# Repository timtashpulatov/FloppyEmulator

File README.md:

# YetAnotherFloppyEmulator
Oh no, not another floppy emulator please

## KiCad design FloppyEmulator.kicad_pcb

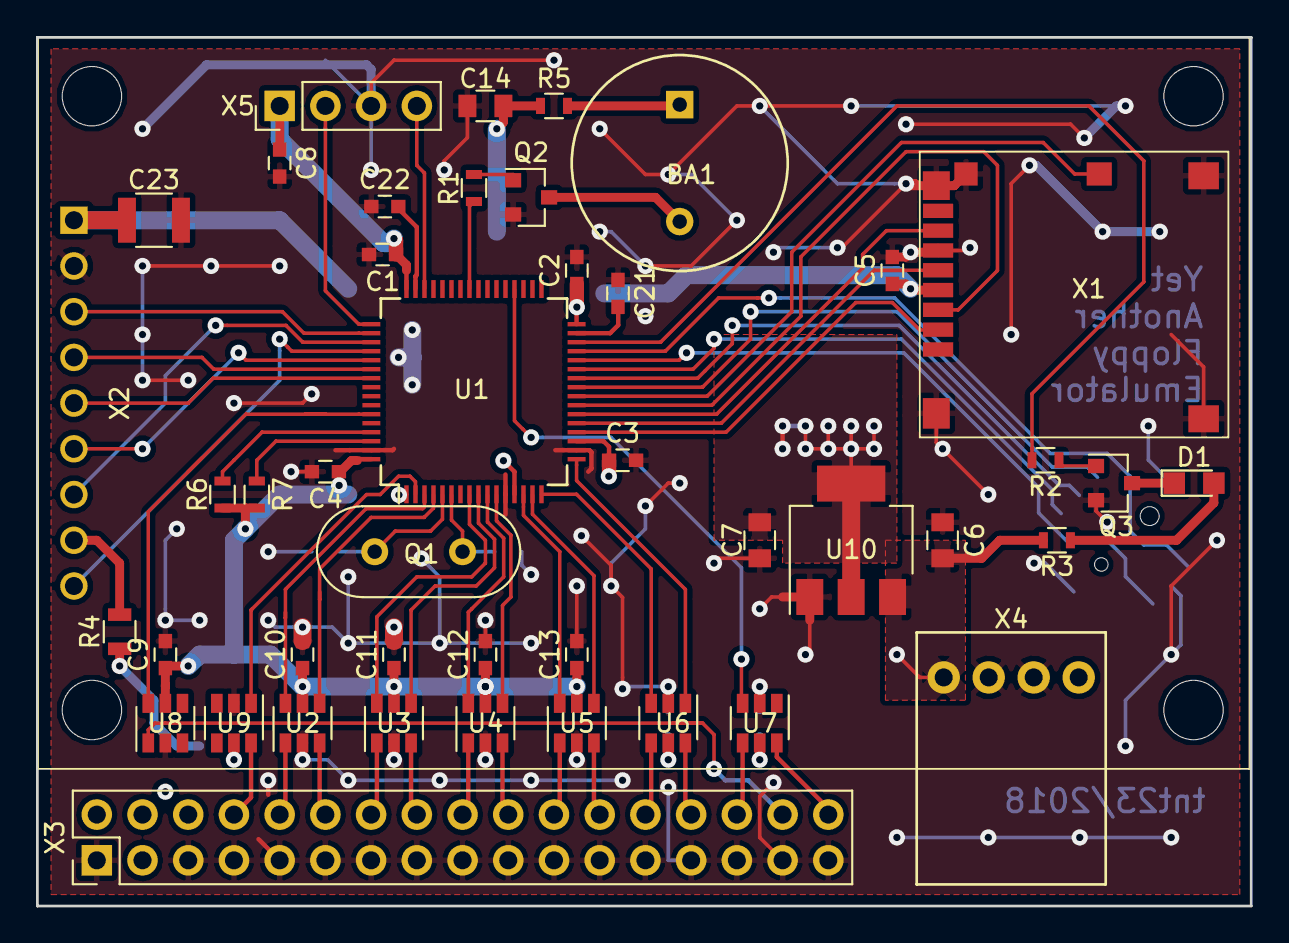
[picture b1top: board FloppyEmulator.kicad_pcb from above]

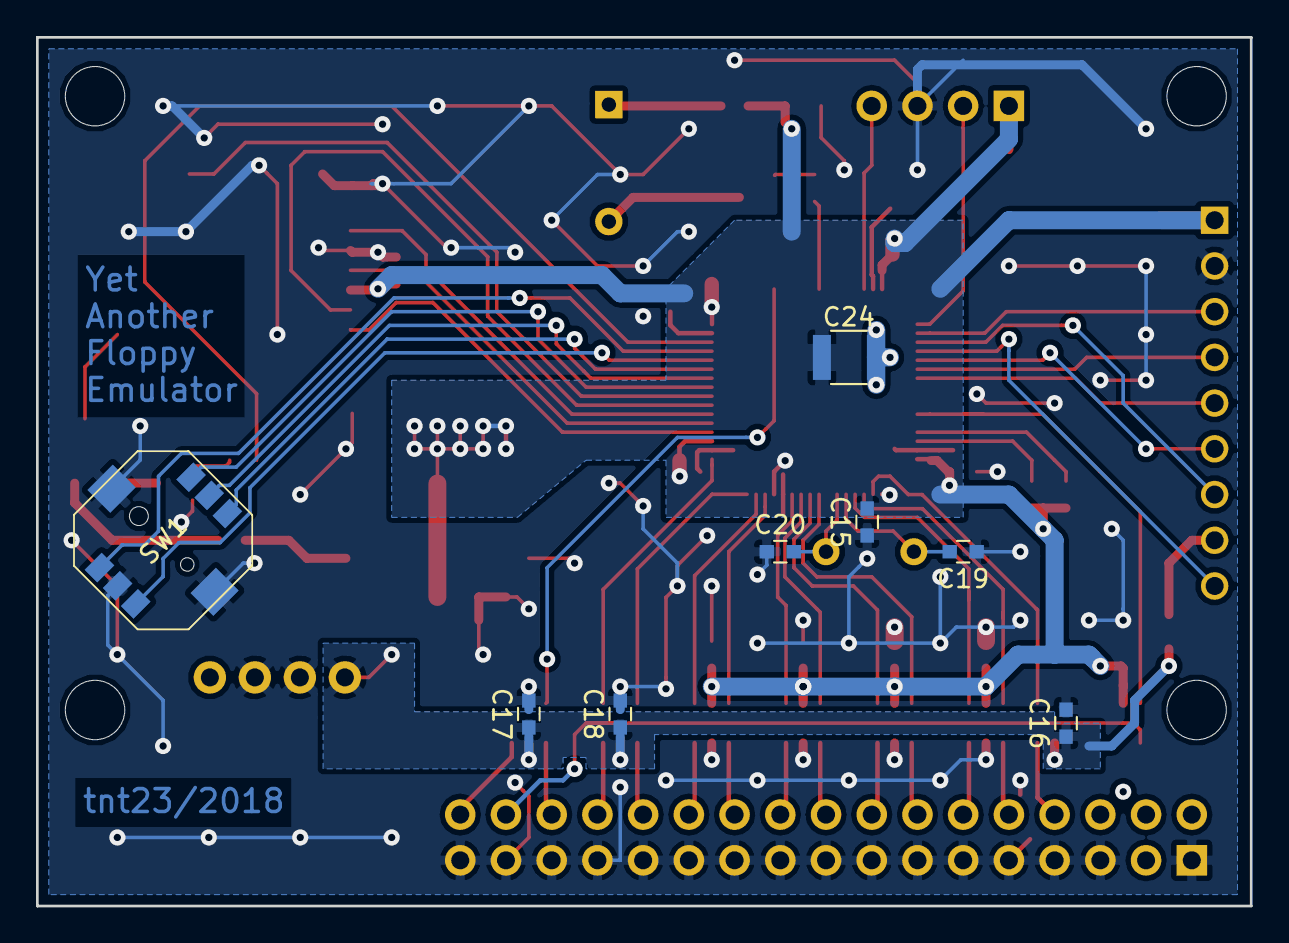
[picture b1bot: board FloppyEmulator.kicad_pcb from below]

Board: 2 copper layers, 67.4 x 48.3 mm, 52 parts (8 on the bottom side), 63 nets.

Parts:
BA1: HCM1206A
C1, C2, C3, C4, C5, C8, C9, C10, C11, C12, C13, C15, C16, C17, C18, C21, C22: 0,1; C_0603
C6, C7, C14: 2u2; C_0805
C19, C20: 15pF; C_0603
C23, C24: 10u; C_1210
D1: LED_ALT; LED_0805
Q1: Crystal_GND24; Crystal_HC49-U_Vertical
Q2, Q3: BC817; SOT-23
R1, R2: 10K; R_0603
R3: 220; R_0603
R4: TBD; R_0805
R5: TBD; R_0603
R6, R7: DNF; R_0603
SW1: ALPS_5WAY; ALPS_SKRHABE010
U1: STM32F405RGTx; LQFP-64_10x10mm_Pitch0.5mm
U2, U3, U4, U5, U6, U7, U8, U9: SN74LVC2G07; SOT-23-6
U10: AP1117-15; SOT-223-3_TabPin2
X1: Micro_SD_Card_Det; MOLEX_5027740891
X2: Conn_01x09; QVGA_LCD_9pin
X3: Conn_02x17_Odd_Even; Pin_Header_Straight_2x17_Pitch2.54mm
X4: TE 171826-4; 171826-4
X5: SWD; Pin_Header_Straight_1x04_Pitch2.54mm

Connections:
+3V3: C1.1, C2.1, C3.1, C4.1, C5.1, C7.1, C8.1, C9.1, C10.1, C11.1, C12.1, C13.1, C14.1, C15.2, C23.1, C24.1, R5.2, R6.2, R7.2, U1.1, U1.13, U1.19, U1.32, U1.48, U1.64, U2.5, U3.5, U4.5, U5.5, U8.5, U10.2, X1.4, X2.1, X5.1
+5VDC: C6.1, C16.1, C17.1, C18.1, R3.2, R4.1, U6.5, U7.5, U9.5, U10.3, X4.1
/BACKLIGHT: R4.2, X2.8
/BEEP: R1.2, U1.41
/BUTTON1: SW1.6, U1.29
/BUTTON2: SW1.1, U1.27
/BUTTON3: SW1.3, U1.25
/BUTTON4: SW1.4, U1.28
/BUTTON5: SW1.2, U1.26
/CARD_DETECT: U1.24, X1.10
/DIR: U1.11, U4.4
/INDEX: U1.2, U9.1
/LCD_DC: U1.55, X2.5
/LCD_RESET: U1.54, X2.4
/LED1: R2.2, U1.30
/OSC_IN: C19.2, Q1.2, U1.5
/OSC_OUT: C20.2, Q1.1, U1.6
/SEL0: U1.3, U2.6
/SEL1: U1.4, U2.4
/SEL2: U1.8, U3.6
/SEL3: U1.9, U3.4
/SIDE: U1.59, U8.6
/STEP: U1.10, U4.6
/SWCLK: U1.49, X5.2
/SWDIO: U1.46, X5.4
/TRACK0: U1.16, U6.3
/VCAP1: C21.2, U1.31
/VCAP2: C22.2, U1.47
/WPROT: U1.17, U6.1
/WRDATA: U1.14, U5.6
/WRGATE: U1.15, U5.4
GND: C1.2, C2.2, C3.2, C4.2, C5.2, C6.2, C7.2, C8.2, C9.2, C10.2, C11.2, C12.2, C13.2, C14.2, C15.1, C16.2, C17.2, C18.2, C19.1, C20.1, C21.1, C22.1, C23.2, C24.2, Q2.2, Q3.2, SW1.5, SW1.7, U1.12, U1.18, U1.63, U2.2, U3.2, U4.2, U5.2, U6.2, U7.2, U8.2, U9.2, U10.1, X1.6, X1.9, X1.11, X2.2, X3.1, X3.5, X3.7, X3.9, X3.11, X3.13, X3.15, X3.17, X3.19, X3.21, X3.23, X3.25, X3.27, X3.29, X3.31, X3.33, X4.2, X4.3, X5.3
unnamed: BA1.1, R5.1
unnamed: BA1.2, Q2.3
unnamed: D1.1, Q3.3
unnamed: D1.2, R3.1
unnamed: Q2.1, R1.1
unnamed: Q3.1, R2.1
unnamed: U2.1, X3.10
unnamed: U2.3, X3.12
unnamed: U3.1, X3.14
unnamed: U3.3, X3.16
unnamed: U4.1, X3.18
unnamed: U4.3, X3.20
unnamed: U5.1, X3.22
unnamed: U5.3, X3.24
unnamed: U6.4, X3.26
unnamed: U6.6, X3.28
unnamed: U7.4, X3.30
unnamed: U7.6, X3.34
unnamed: U8.1, X3.32
unnamed: U9.6, X3.8
SCL: R6.1, U1.61
SDA: R7.1, U1.62
SPI1_MISO: U1.22, X1.7
SPI1_MOSI: U1.23, X1.3
SPI1_NSS: U1.20, X1.2
SPI1_SCK: U1.21, X1.5
SPI2_MOSI: U1.36, U7.3
SPI3_MISO: U1.52, X2.9
SPI3_MOSI: U1.53, X2.6
SPI3_NSS: U1.50, X2.3
SPI3_SCK: U1.51, X2.7

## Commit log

2017-12-28 Bit of update
2017-12-28 Signals assigned
2017-12-28 Add microSD connector datasheet
2017-12-28 Add footprint library with LCD and microSD
2017-12-28 Draft components placement
2017-12-28 Add microSD footprint. Update schematic and PCB
2017-12-28 Add docs
2017-12-28 Add ALPS 5-way joystick
2017-12-28 Add FloppyEmulator library
2017-12-28 Add CubeMX layout pic. PCB remastered
2017-12-31 Layout and schematic update
2017-12-31 More docs and 3d models
2018-01-02 Caps added. PCB update
2018-01-02 Routing WIP
2018-01-02 Backlight
2018-01-02 Copper pours
2018-01-02 Add HCM1206A beeper
2018-01-02 Add I2C
2018-01-02 Bit of 3d models
2018-01-03 Add I2C pullups
2018-01-03 Cleanups
2018-01-03 Credits
2018-01-03 Even more cleanups
2018-01-03 LCD add-on board size corrected
2018-01-03 README.md updated
2018-01-03 Images
2018-01-03 PCB trimmed to updated LCD shield
2018-01-03 Copper cleanup
2018-01-03 More cleanups
2018-01-03 Fixed LCD shield dimensions
2018-01-03 PCB size adjusted
2018-01-04 Schematic cleanup
2018-01-04 More final touches
2018-01-09 Gerbers
2018-01-18 Add Errata.txt
2018-01-18 Add footprints for microSD and beeper
2018-01-18 Giraffe!
